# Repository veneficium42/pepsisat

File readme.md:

# PEPSISat
## Positioning Efficiente e Portatile su Sonda tramite Immagini Satellitari

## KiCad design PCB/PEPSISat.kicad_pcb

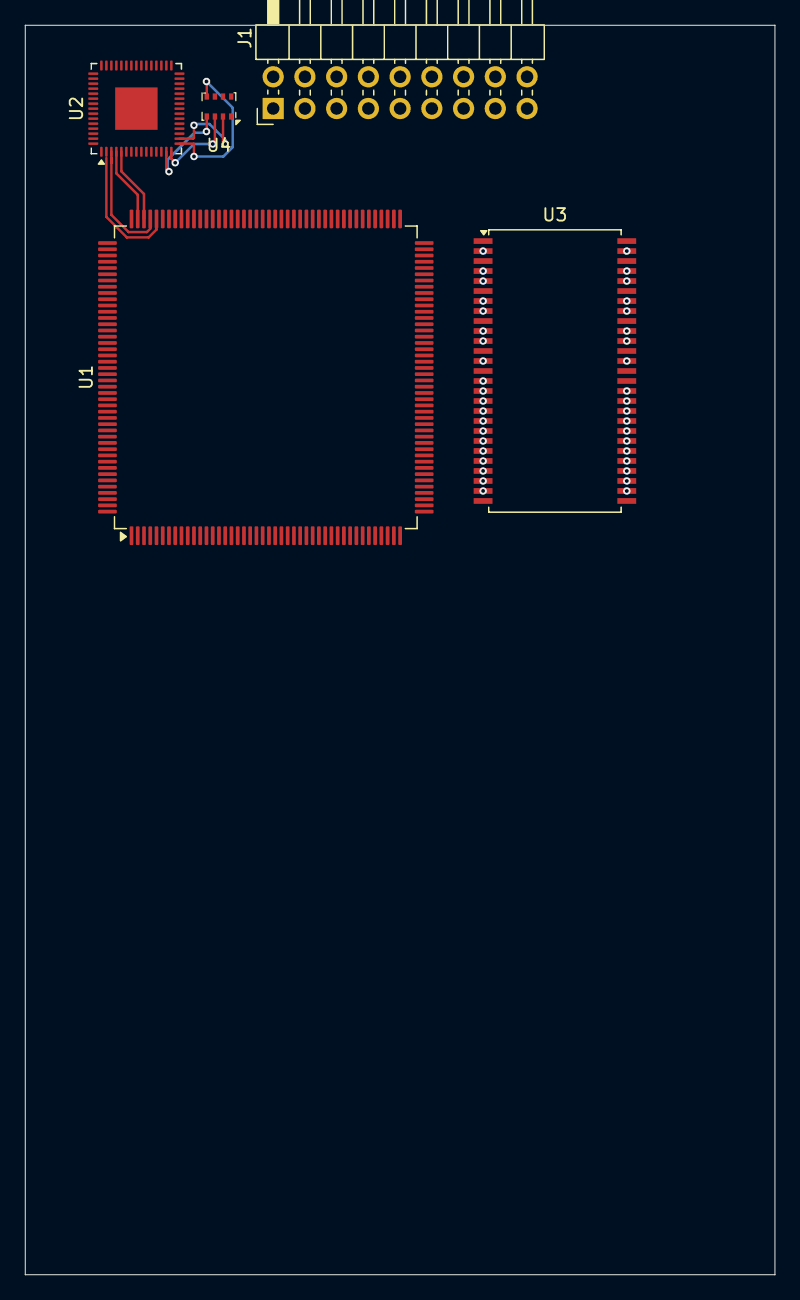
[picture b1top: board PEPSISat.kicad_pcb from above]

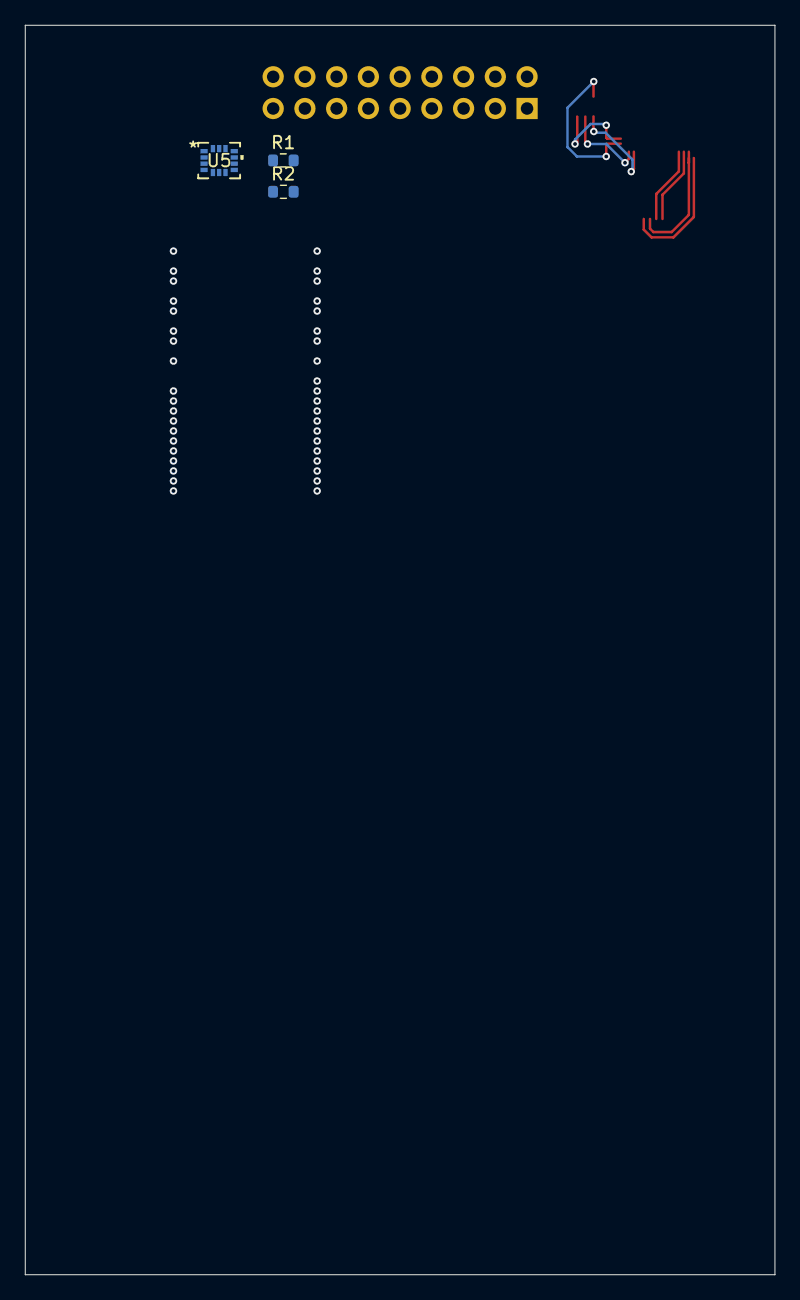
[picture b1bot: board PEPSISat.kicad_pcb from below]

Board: 2 copper layers, 60.0 x 100.0 mm, 8 parts (3 on the bottom side), 70 nets.

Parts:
J1: Conn_02x09_Counter_Clockwise; PinHeader_2x09_P2.54mm_Horizontal
R1, R2: 4.7kR; R_0603_1608Metric
U1: STM32H747IITx; LQFP-176_24x24mm_P0.5mm
U2: RP2350A; QFN-60-1EP_7x7mm_P0.4mm_EP3.4x3.4mm
U3: MT48LC16M16A2P; TSOP-II-54_22.2x10.16mm_P0.8mm
U4: BMP280; Bosch_LGA-8_2x2.5mm_P0.65mm_ClockwisePinNumbering
U5: LSM6DSOXTR; LGA-14L_STM

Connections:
3V3: R1.1, R2.1, U5.5 (VDDIO), U5.8 (VDD), U5.12 (CS)
/DCMI.D0: J1.15, U1.122 (PC6)
/DCMI.D1: J1.16, U1.123 (PC7)
/DCMI.D2: J1.13, U1.124 (PC8)
/DCMI.D3: J1.14, U1.125 (PC9)
/DCMI.D4: J1.11, U1.3 (PE4)
/DCMI.D5: J1.12, U1.146 (PD3)
/DCMI.D6: J1.9, U1.4 (PE5)
/DCMI.D7: J1.10, U1.5 (PE6)
/DCMI.HS: J1.5, U1.50 (PA5)
/DCMI.PC: J1.8, U1.51 (PA6)
/DCMI.SCL: J1.4, U1.168 (PB8)
/DCMI.SDA: J1.3, U1.169 (PB9)
/DCMI.VS: J1.6, U1.166 (PB7)
/DCMI.XC: J1.7, U1.127 (PA8)
/FMC.BA0: U1.114 (PG4), U3.20 (BA0)
/FMC.BA1: U1.115 (PG5), U3.21 (BA1)
/FMC.CKE: U1.54 (PC5), U3.37 (CKE)
/FMC.CLK: U1.118 (PG8), U3.38 (CLK)
/FMC.~CAS: U1.161 (PG15), U3.17 (~CAS)
/FMC.~CS: U1.53 (PC4), U3.19 (~CS)
/FMC.~RAS: U1.58 (PF11), U3.18 (~RAS)
/FMC.~WE: U1.52 (PA7), U3.16 (~WE)
/FMC_A0: U1.18 (PF0), U3.23 (A0)
/FMC_A1: U1.19 (PF1), U3.24 (A1)
/FMC_A2: U1.20 (PF2), U3.25 (A2)
/FMC_A3: U1.21 (PF3), U3.26 (A3)
/FMC_A4: U1.22 (PF4), U3.29 (A4)
/FMC_A5: U1.23 (PF5), U3.30 (A5)
/FMC_A6: U1.59 (PF12), U3.31 (A6)
/FMC_A7: U1.60 (PF13), U3.32 (A7)
/FMC_A8: U1.61 (PF14), U3.33 (A8)
/FMC_A9: U1.62 (PF15), U3.34 (A9)
/FMC_A10: U1.63 (PG0), U3.22 (A10)
/FMC_A11: U1.66 (PG1), U3.35 (A11)
/FMC_A12: U1.110 (PG2), U3.36 (A12)
/FMC_D0: U1.97 (PD14), U3.2 (DQ0)
/FMC_D1: U1.98 (PD15), U3.4 (DQ1)
/FMC_D2: U1.143 (PD0), U3.5 (DQ2)
/FMC_D3: U1.144 (PD1), U3.7 (DQ3)
/FMC_D4: U1.67 (PE7), U3.8 (DQ4)
/FMC_D5: U1.68 (PE8), U3.10 (DQ5)
/FMC_D6: U1.69 (PE9), U3.11 (DQ6)
/FMC_D7: U1.72 (PE10), U3.13 (DQ7)
/FMC_D8: U1.73 (PE11), U3.42 (DQ8)
/FMC_D9: U1.74 (PE12), U3.44 (DQ9)
/FMC_D10: U1.75 (PE13), U3.45 (DQ10)
/FMC_D11: U1.76 (PE14), U3.47 (DQ11)
/FMC_D12: U1.77 (PE15), U3.48 (DQ12)
/FMC_D13: U1.89 (PD8), U3.50 (DQ13)
/FMC_D14: U1.90 (PD9), U3.51 (DQ14)
/FMC_D15: U1.91 (PD10), U3.53 (DQ15)
/UART.CTS_{ST}-RTS_{RP}: U1.130 (PA11), U2.5 (GPIO3)
/UART.RTS_{ST}-CTS_{RP}: U1.131 (PA12), U2.4 (GPIO2)
/UART.RX: U1.129 (PA10), U2.3 (GPIO1)
/UART.TX: U1.128 (PA9), U2.2 (GPIO0)
GND: R2.2, U1.95 (PD12), U5.1 (SDO/SA0), U5.6 (GND), U5.7 (GND), U5.13 (SCL)
unnamed: R1.2, U1.96 (PD13), U5.14 (SDA)
unnamed: U1.6 (VSS), U1.12 (VSS), U1.24 (VSS), U1.45 (VSS), U1.47 (VSS), U1.64 (VSS), U1.70 (VSS), U1.81 (VSS), U1.83 (VSS), U1.93 (VSS), U1.100 (VSS), U1.112 (VSS), U1.119 (VSS), U1.134 (VSS), U1.137 (VSS), U1.151 (VSS), U1.159 (VSS), U1.173 (VSS)
unnamed: U1.105 (VSSDSI), U1.109 (VSSDSI)
unnamed: U2.6 (DVDD), U2.23 (DVDD), U2.39 (DVDD)
unnamed: U2.14 (GPIO10), U4.4 (SCK)
unnamed: U2.15 (GPIO11), U4.3 (SDI)
unnamed: U2.16 (GPIO12), U4.5 (SDO)
unnamed: U2.17 (GPIO13), U4.2 (CSB)
unnamed: U2.1 (IOVDD), U2.11 (IOVDD), U2.20 (IOVDD), U2.30 (IOVDD), U2.38 (IOVDD), U2.45 (IOVDD)
unnamed: U3.1 (VDD), U3.14 (VDD), U3.27 (VDD)
unnamed: U3.3 (VDDQ), U3.9 (VDDQ), U3.43 (VDDQ), U3.49 (VDDQ)
unnamed: U3.28 (VSS), U3.41 (VSS), U3.54 (VSS)
unnamed: U3.6 (VSSQ), U3.12 (VSSQ), U3.46 (VSSQ), U3.52 (VSSQ)

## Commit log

2026-01-04 initial platformio example (blinking LED)
2026-01-15 added stm32 image processing library
2026-02-24 Added KiCad project files
2026-02-24 KiCad
2026-02-26 KiCad - RAM D&A bus
    Added RAM connection for Data and Address bus.
2026-02-26 Added RP2350 datasheet
2026-04-29 New configuration
    New configuration (Test2) for images and SD card operations (FAT32).
